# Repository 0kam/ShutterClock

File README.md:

<p align="center">
  <picture>
    <source media="(prefers-color-scheme: dark)" srcset="docs/assets/logo/logo_dark_800.png">
    
  </picture>
</p>

# ShutterClock

定点カメラ（タイムラプス・フェノロジー観測）用の低消費電力インターバルタイマです。
Nikon デジタル一眼レフをリモート端子から有線レリーズし、12 V ソーラー充電バッテリーからカメラへ給電することもできます。
時刻合わせ・撮影スケジュール設定・撮影ログ回収は、スマホ（Android Chrome）の Web Bluetooth ページで行います。
積雪深ロガー [SnowGauge](https://github.com/0kam/SnowGauge) の姉妹プロジェクトです。

*ShutterClock is a low-power BLE interval timer for fixed-point cameras: XIAO nRF52840 (Zephyr), wired Nikon remote release via optocouplers, optional camera power from a 12 V solar battery, Web Bluetooth field app. Documentation is in Japanese.*

## 状態（2026-10-11）

基板 v1.0 を JLCPCB に発注済み（5 枚、10 月中旬到着予定）、部品も発注済み。ファームウェア（`firmware/`、ビルド済み）とスマホアプリ（https://0kam.github.io/ShutterClock/app/ 、[デモ表示](https://0kam.github.io/ShutterClock/app/?demo=1)）の初版あり、実機検証はこれから。初期決定事項と未決事項を [設計仕様書 v0.17](ShutterClock_設計仕様書_v0.17.md) にまとめています。
対象機種は D7200・D7500（必須）と D7000・D7100・D800・D810（任意）。D7500 の消費電流は実測済み。次は部品・基板の到着後に実機でファームウェアを動かし、降圧モジュール・時計保持経路・撮影検出を確認します。

## 開発者向け

- 設計仕様書（要件・設計判断・未決事項・改版履歴）: [ShutterClock_設計仕様書_v0.17.md](ShutterClock_設計仕様書_v0.17.md)
- 部品購入リスト: [docs/01_parts.md](docs/01_parts.md)（[CSV](docs/01_parts.csv)、5 台分 [docs/01_order_5sets.csv](docs/01_order_5sets.csv)）
- 組み立てガイド（配置図・はんだ付け順・通電チェック）: [docs/02_assembly.md](docs/02_assembly.md)
- 基板: [pcb/README.md](pcb/README.md)（ピンマップの正）
- ファームウェア: [firmware/README.md](firmware/README.md)
- アプリ: [docs/app/README.md](docs/app/README.md)
- SnowGauge から流用したファイルの一覧: [PROVENANCE.md](PROVENANCE.md)
- 作業引き継ぎ（AI エージェント向け）: [CLAUDE.md](CLAUDE.md)

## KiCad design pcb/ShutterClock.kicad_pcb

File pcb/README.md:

# ShutterClock PCB

- **v1.2 (2026-10-21, not ordered)**: v1.1 + battery-backed RTC. Board grown to **100 x 100 mm**
  (mounting holes 93 x 93 mm); a 12 mm strip at the bottom carries **U5** Akizuki AE-RX8900
  (RX8900CE DTCXO RTC, I2C 0x32 on the XIAO D4 = SDA / D5 = SCL, VDD from 3V3_SYS, FOE tied to
  GND so FOUT stays off), **BT1** CH243-2032LF vertical CR2032 holder and **D7** 1N4148 in series
  with the cell (the RX8900 has an internal VDD -> VBAT charge path; a CR2032 must not be charged).
  SW1 and ZD1 moved 1-2 mm right to make room for the I2C / 3V3 tracks along the left edge.
  DRC 0 errors / 0 unconnected. `ShutterClock_v1.2_gerbers.zip`, `render_top.png`,
  `../docs/assembly/placement_top_v1.2.png`. **Open before ordering**: the holder's centre pin is
  assumed to be "+" (drawing CH243-0308 does not mark polarity) - check with a cell and a meter on
  the real part; if the outer pins are "+", swap BT1 pad nets in `generate_board.py`.
- **v1.1 (2026-10-21, not ordered)**: the three v1.0 errata fixed (C1 polarity nets, U2 hole
  pattern 40 x 17.5 mm, F1 clip pins along the fuse axis at 7.0 mm; ZD1 moved 3.5 mm down to make
  room). DRC 0 errors / 0 unconnected (40 silk warnings). Gerbers `ShutterClock_v1.1_gerbers.zip`,
  renders `render_top.png` / `render_bottom.png`, placement map `../docs/assembly/placement_top_v1.1.png`.
  Same outline, mounting holes and connector positions as v1.0, so the v1.0 bench results apply.
- **v1.0 (ordered 2026-10-08, JLCPCB W2026100808086019 / Y14-13437881A, 5 pcs; board #1 assembled
  and bench-tested 2026-10-20)**: `ShutterClock_v1.0_gerbers.zip`, `render_top_v1.0.png` /
  `render_bottom_v1.0.png`. Build the remaining v1.0 boards with the workarounds in
  `../docs/02_assembly.md`.

- Board: **100 x 88 mm**, 2-layer. Bottom layer is a GND pour; most signals on top,
  the VIN trunk and a few long signals on the bottom.
- Mounting: 4x M3 (3.2 mm) holes, centres 3.5 mm from each edge (93 x 81 mm spacing).
- Generated by [generate_board.py](generate_board.py) (+ [tracks.py](tracks.py)) →
  `ShutterClock.kicad_pcb` (KiCad 10). **Never hand-edit the .kicad_pcb.**
  Run: `/Applications/KiCad/KiCad.app/Contents/Frameworks/Python.framework/Versions/Current/bin/python3 generate_board.py`
  then `kicad-cli pcb drc --severity-error --severity-warning --format json --output drc.json ShutterClock.kicad_pcb`
  and `python3 drc_report.py`. Current state: **DRC 0 errors, 0 unconnected** (46 warnings: silkscreen overlaps, library-name notes).
- Gerbers for JLCPCB (2 layers, 1.6 mm, HASL, defaults): see the version list above. Export: `kicad-cli pcb export gerbers --layers F.Cu,B.Cu,F.Paste,B.Paste,F.Silkscreen,B.Silkscreen,F.Mask,B.Mask,Edge_Cuts --subtract-soldermask`, `kicad-cli pcb export drill --format excellon --excellon-units mm --generate-map --map-format gerberx2`, zip the folder. `kicad-cli` = `/Applications/KiCad/KiCad.app/Contents/MacOS/kicad-cli`.
- Circuit: spec v0.11 §6 (independent review applied). BOM: `../docs/01_parts.md`. Assembly guide: `../docs/02_assembly.md` (placement map generated by `../docs/assembly/draw_placement.py`).

## Errata v1.0 (fixed in v1.1)

1. **C1 silkscreen "+" is on the wrong pad.** `generate_board.py` assigns C1 pad 1 (the square
   pad, which the KiCad `CP_Radial` footprint marks "+") to GND and pad 2 to VIN. Electrically the
   board is fine; **mount C1 with its + lead in the right-hand (round) pad**. v1.1: swap the nets
   to `{"1": "VIN", "2": "GND"}` and re-route the two C1 tracks. C3 is correct (pad 1 = CAM_P).
2. **U2 (MBC2596-01) hole pattern is 40.0 x 17.5 mm** (measured on the real module 2026-10-19),
   not the 38 x 16 mm placeholder (±19.0 / ±8.0). v1.0 boards: the module is connected with bent
   tinned wire. v1.1: `fp_buck()` pads at ±20.0 / ±8.75 mm.
3. **F1 fuse clips (FUC-03A): the two pins of one clip lie ALONG the fuse axis**, not across it as
   in `fp_fuseclips()` (pairs 6.7 mm apart across the axis). v1.0 boards: cut one pin per clip and
   solder the other into one hole (keep the outer pin on one clip and the inner pin on the other
   so the clip spacing stays 18 mm), or put an inline fuse holder in the battery + lead and bridge
   the F1 holes. v1.1: rotate the footprint; pin pitch along the axis still to be measured.

## Open items (ordered before bench verification — check these when the boards arrive)

1. ~~U2 hole positions~~ → wrong, see Errata 2.
2. Bench-verify the circuit on the breadboard first (spec §6.5): LM2596 + 4700 µF with the
   D7500 (and D7200), keep-alive follower voltage, shot detection on A1.
3. Independent layout review (as for SnowGauge v1.2) — not done yet.
4. XIAO SMD-pad clearance to the KA_EN / CAM_EN tracks is at the 0.2 mm minimum; fine for
   JLCPCB but do not tighten.

## Firmware pin map (single source of truth for the board)

| XIAO pin | Net | Function |
|---|---|---|
| A0 (D0) | ADC_NODE | Battery voltage: VIN × 100k/(1M+100k) (ungated divider, 100 nF). Reading × 11 |
| A1 (D1) | A1_NODE | Camera current: 0.1 Ω low-side shunt in the camera return (CAM_N), 10 kΩ + 100 nF. 1 A = 0.1 V |
| D2 | AF_DRV | PC817 U4 (AF / half-press) via 1 kΩ. High = pressed |
| D7 | CAM_EN | Camera supply: Q3 → Q2 → MBC2596-01 (9.4 V) → 1N5822 → CAM_P. High = on |
| D8 | SHUT_DRV | PC817 U3 (SHUTTER / full-press) via 1 kΩ. High = pressed |
| D9 | BTN | Test-shot / BLE button SW1 to GND (enable the internal pull-up) |
| D10 | KA_EN | Keep-alive path: Q6 → Q5 → 10 Ω → Q7 follower (≈ 7.3–8.5 V) → CAM_P. High = on |
| 3V3 | 3V3_SYS | From U1 (NJW4181U3-33B) through JP1 |
| GND | GND | |
| D4 / D5 | SDA / SCL | v1.2: RX8900 RTC module U5 (i2c1). Unused on v1.0 / v1.1 |
| D3, D6, 5V | — | unused |

Rules: never drive CAM_EN and KA_EN so that the camera is released on the keep-alive
path; enter keep-alive only from CAM_EN = on; drop to CAM_EN = on if A1 shows > 50 mA
during keep-alive; low-battery cutoff 11.5 V.

## Connectors and jumpers

- J1 (5.08 mm screw terminal, bottom-left): battery + / − (12 V lead-acid / LiFePO4; fuse F1 5 A, Q1 reverse protection, 2x P4KE15A TVS)
- J2 (5.08 mm screw terminal, bottom-right): camera + / − → Nikon EP-5B cable. The − side is the sense shunt — keep it as the only camera ground.
- J3 (3.5 mm stereo jack, right edge): tip = SHUTTER, ring = AF, sleeve = common → off-the-shelf 3.5 mm → MC-DC2 / 10-pin release cables (verify the cable's pinout with a meter)
- JP1 (near the XIAO): shunt fitted normally; **remove before connecting USB** to the XIAO (same rule as SnowGauge)
- JP2 (below Q3): shunt fitted = camera supply always on (bypasses Q3)
- U2: 4-pin module socket positions; set the trimpot to **9.4 V** and remove the module's LED before fitting

## Silkscreen notes

"REMOVE JP1 BEFORE USB", "U2: SET 9.4V, REMOVE LED", "JP2=ALWAYS ON", battery and camera polarity, diode cathodes marked "K".

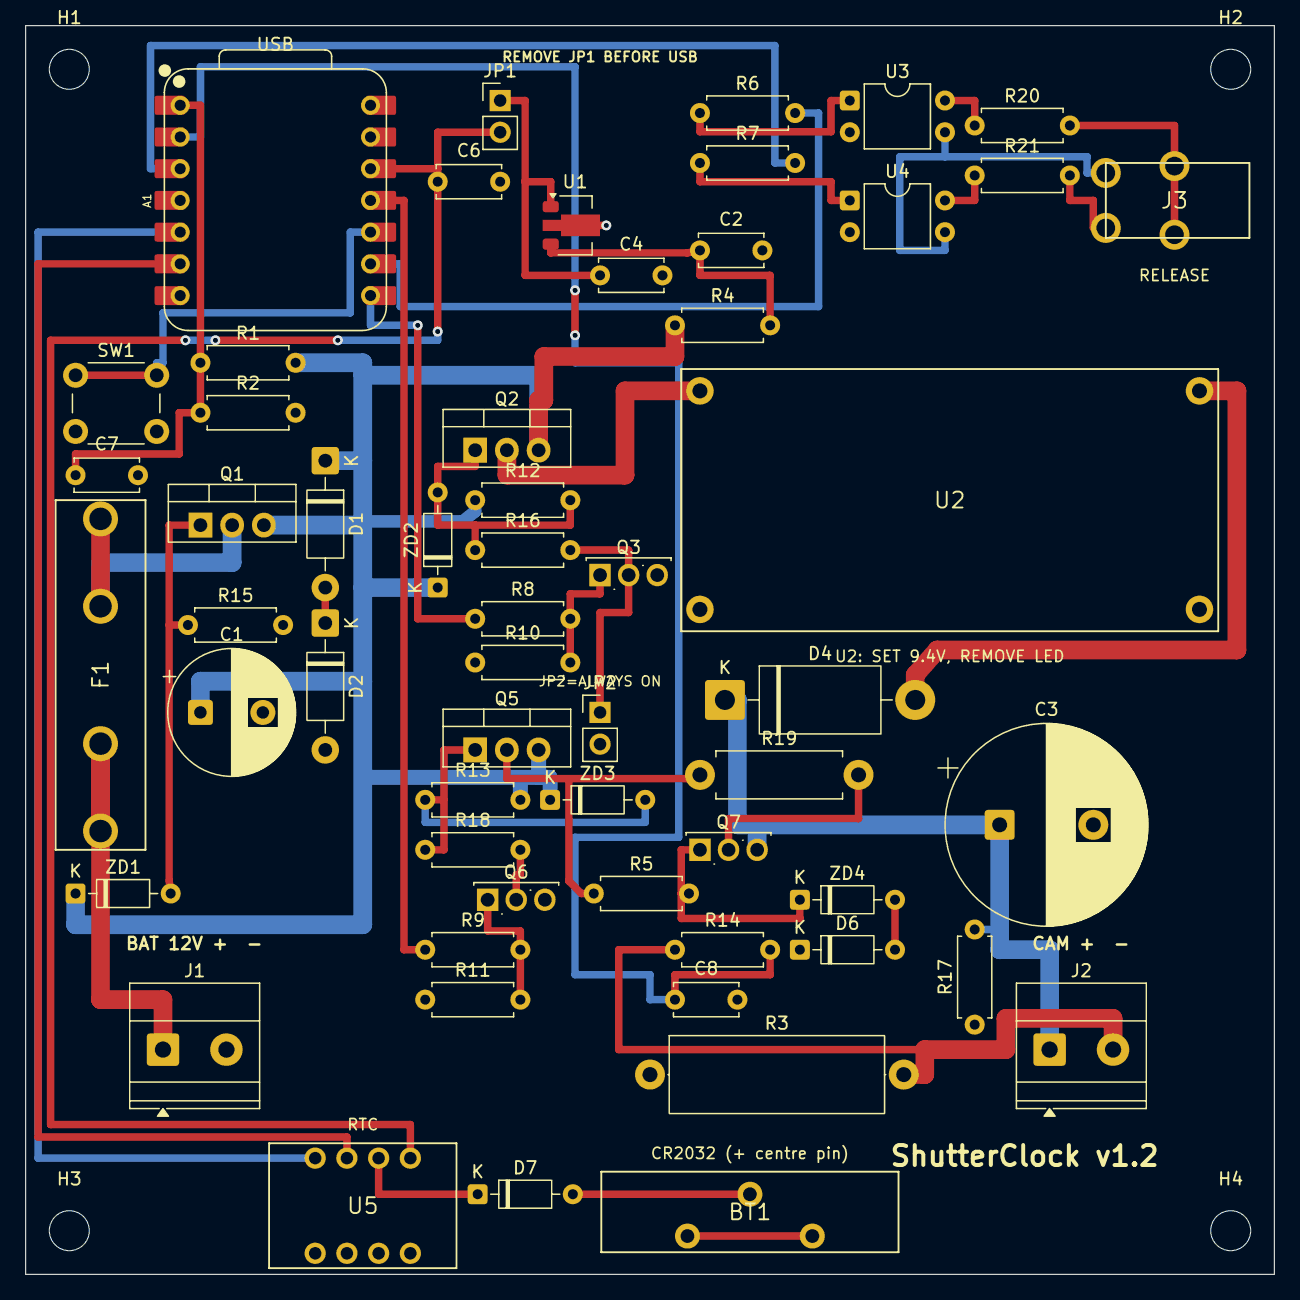
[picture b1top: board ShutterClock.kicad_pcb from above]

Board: 2 copper layers, 100.0 x 100.0 mm, 61 parts (0 on the bottom side), 41 nets.

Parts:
A1: XIAO nRF52840; XIAO-nRF52840-DIP
BT1: CR2032; CH243-2032LF
C1: 100u/50V; CP_Radial_D10.0mm_P5.00mm
C2: 10u; C_Disc_D5.0mm_W2.5mm_P5.00mm
C3: 4700u/16V; CP_Radial_D16.0mm_P7.50mm
C4: 2.2u; C_Disc_D5.0mm_W2.5mm_P5.00mm
C6, C7, C8: 0.1u; C_Disc_D5.0mm_W2.5mm_P5.00mm
D1, D2: P4KE15A; D_DO-41_SOD81_P10.16mm_Horizontal
D4: 1N5822; D_DO-201AD_P15.24mm_Horizontal
D6, D7: 1N4148; D_DO-35_SOD27_P7.62mm_Horizontal
F1: 5A; FUC-03A_x2_5x20
H1, H2, H3, H4: M3; MountingHole_3.2mm_M3
J1: BATTERY 12V; TerminalBlock_Phoenix_MKDS-1,5-2-5.08_1x02_P5.08mm_Horizont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
J2: CAMERA EP-5B; TerminalBlock_Phoenix_MKDS-1,5-2-5.08_1x02_P5.08mm_Horizont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
J3: 3.5mm RELEASE; MJ-8435
JP1: JP1 3V3; PinHeader_1x02_P2.54mm_Vertical
JP2: JP2 ALWAYS ON; PinHeader_1x02_P2.54mm_Vertical
Q1: 2SJ334 REV; TO-220-3_Vertical
Q2: 2SJ334 CAM; TO-220-3_Vertical
Q3, Q6: 2SK4017; TO-251-3_Vertical
Q5: 2SJ334 KA; TO-220-3_Vertical
Q7: 2SK4017 KA; TO-251-3_Vertical
R1, R15, R17: 1M; R_Axial_DIN0207_L6.3mm_D2.5mm_P7.62mm_Horizontal
R2, R10, R11, R12, R13: 100k; R_Axial_DIN0207_L6.3mm_D2.5mm_P7.62mm_Horizontal
R3: 0.1R 3W; R_Axial_DIN0617_L17.0mm_D6.0mm_P20.32mm_Horizontal
R4, R20, R21: 100; R_Axial_DIN0207_L6.3mm_D2.5mm_P7.62mm_Horizontal
R5: 47k; R_Axial_DIN0207_L6.3mm_D2.5mm_P7.62mm_Horizontal
R6, R7, R8, R9: 1k; R_Axial_DIN0207_L6.3mm_D2.5mm_P7.62mm_Horizontal
R14: 10k; R_Axial_DIN0207_L6.3mm_D2.5mm_P7.62mm_Horizontal
R16, R18: 33k; R_Axial_DIN0207_L6.3mm_D2.5mm_P7.62mm_Horizontal
R19: 10R 1W; R_Axial_DIN0411_L9.9mm_D3.6mm_P12.70mm_Horizontal
SW1: TEST; SW_PUSH_6mm
U1: NJW4181U3-33B; SOT-89-3
U2: MBC2596-01 9.4V; MBC2596-01
U3: PC817 SHUTTER; DIP-4_W7.62mm
U4: PC817 AF; DIP-4_W7.62mm
U5: AE-RX8900
ZD1, ZD2, ZD3: 15V; D_DO-35_SOD27_P7.62mm_Horizontal
ZD4: 9.1V; D_DO-35_SOD27_P7.62mm_Horizontal

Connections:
3V3_LDO: C4.1, JP1.1, U1.1
3V3_SYS: A1.12, C6.1, JP1.2, U5.8
A1_NODE: A1.2, C8.1, R14.2
ADC_NODE: A1.1, C7.1, R1.1, R2.1
AF_C: R21.1, U4.4
AF_DRV: A1.3, R7.2
AF_LED_A: R7.1, U4.1
BAT_RAW: F1.1, J1.1
BTN: A1.10, SW1.1
BT_P: BT1.1, D7.2
BUCK_IN: Q2.2, U2.INP
BUCK_OUT: D4.2, U2.OUTP
CAM_EN: A1.8, R8.1
CAM_N: J2.2, R3.2, R14.1
CAM_P: C3.1, D4.1, J2.1, Q7.3, R17.2
F_OUT: F1.2, Q1.2
GND: A1.13, BT1.2, C1.2, C2.2, C3.2, C4.2, C6.2, C7.2, C8.2, D2.2, D6.1, J1.2, JP2.2, Q3.3, Q6.3, R2.2, R3.1, R10.1, R11.1, R15.2, R17.1, SW1.2, U1.2, U2.INN, U2.OUTN, U3.2, U4.2, U5.1, U5.4
JACK_RING: J3.3, R21.2
JACK_SLEEVE: J3.1, U3.3, U4.3
JACK_TIP: J3.2, R20.2
KA_EN: A1.11, R9.1
KA_SW: Q5.2, R5.1, R19.1
LDO_IN: C2.1, R4.2, U1.3
Q1_G: Q1.1, R15.1, ZD1.2
Q2_DRV: JP2.1, Q3.2, R16.2
Q2_G: Q2.1, R12.2, R16.1, ZD2.2
Q3_G: Q3.1, R8.2, R10.2
Q5_DRV: Q6.2, R18.2
Q5_G: Q5.1, R13.1, R18.1, ZD3.2
Q6_G: Q6.1, R9.2, R11.2
Q7_D: Q7.2, R19.2
Q7_G: Q7.1, R5.2, ZD4.1
SCL: A1.6, U5.6
SDA: A1.5, U5.5
SHUT_C: R20.1, U3.4
SHUT_DRV: A1.9, R6.2
SHUT_LED_A: R6.1, U3.1
TVS_MID: D1.2, D2.1
VBAT_RTC: D7.1, U5.7
VIN: C1.1, D1.1, Q1.3, Q2.3, Q5.3, R1.2, R4.1, R12.1, R13.2, ZD1.1, ZD2.1, ZD3.1
ZD_MID: D6.2, ZD4.2

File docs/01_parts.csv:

区分,記号,部品,値/型番,数量,購入先リンク,備考
回路,A1,マイコン（BLE）,Seeed XIAO nRF52840（非Sense）,1,https://akizukidenshi.com/catalog/g/g117341/,¥1780。予備+1推奨
回路,U1,3.3V LDO（常時ON）,NJW4181U3-33B (SOT-89),1,https://akizukidenshi.com/catalog/g/g113996/,¥60。表面実装。ブレッドボードではAE-SOT89に載せる
回路,U2,カメラ用9V降圧,MBC2596-01 (LM2596-ADJ),2,https://akizukidenshi.com/catalog/g/g131750/,¥1900。1個予備。在庫僅少（10月中旬入荷）。9.4Vに調整・LED除去
回路,"Q1,Q2,Q5",P-ch MOSFET,2SJ334,3,https://akizukidenshi.com/catalog/g/g102846/,¥110。G-D-S
回路,"Q3,Q6,Q7",N-ch MOSFET,2SK4017(Q),3,https://akizukidenshi.com/catalog/g/g107597/,¥30。G-D-S
回路,"ZD1,ZD2,ZD3",15Vツェナー,GDZJ15C 500mW,3,https://akizukidenshi.com/catalog/g/g115169/,10本¥90
回路,ZD4,9.1Vツェナー（時計保持フォロワ基準）,BZX55C9V1 500mW,1,https://akizukidenshi.com/catalog/g/g115721/,20本¥100。1N4148と直列
回路,D6,ZD4と直列,1N4148,1,https://akizukidenshi.com/catalog/g/g100941/,50本¥200
回路,"D1,D2",TVS（2本直列）,P4KE15A,2,https://akizukidenshi.com/catalog/g/g129633/,10本¥150
回路,D4,ショットキー（U2出力逆流防止）,1N5822 40V3A,1,https://akizukidenshi.com/catalog/g/g102229/,10本¥350
回路,F1,ヒューズ,MF51NR 250V5A 5.2x20mm,1,https://akizukidenshi.com/catalog/g/g107131/,¥40
回路,F1ホルダ,ヒューズクリップ,FUC-03A,2,https://akizukidenshi.com/catalog/g/g110521/,¥20。2個で1本分
回路,R3,電流検出抵抗,0.1Ω 3W ±1% RSMF3BR100F,1,https://akizukidenshi.com/catalog/g/g111011/,¥20
回路,"U3,U4",フォトカプラ,PC817 (PC817X3NSZ1B),2,https://akizukidenshi.com/catalog/g/g113765/,¥30。在庫僅少。代替UPC817CG 116090
回路,J3,3.5mmステレオジャック,MJ-8435,1,https://akizukidenshi.com/catalog/g/g109060/,¥90
回路,"JP1,JP2",ジャンパ（USB時外す/常時ON）,ピンヘッダ1x2+ジャンパピン,2,https://akizukidenshi.com/catalog/g/g103691/,ジャンパピンのコード要確認
回路,SW1,タクトスイッチ,6mm DTS-63-N-V-BLK,1,https://akizukidenshi.com/catalog/g/g103647/,¥15
回路,C1,入力バルク,100μF/50V ハイブリッド Rubycon PZF,1,https://akizukidenshi.com/catalog/g/g116871/,¥80
回路,C2,U1入力RC,10μF/50V 積セラ 5mm,1,https://akizukidenshi.com/catalog/g/g108155/,¥60
回路,C3,カメラ9V側バルク,4700μF/16V Rubycon ZLH,1,https://akizukidenshi.com/catalog/g/g114096/,¥100
回路,C4,U1出力,2.2μF/50V 積セラ 5mm,1,https://akizukidenshi.com/catalog/g/g108152/,¥30
回路,C6-C8,パスコン・ADCフィルタ,0.1μF/50V 積セラ,3,https://akizukidenshi.com/catalog/g/g113582/,10個¥100
回路,R4,U1入力RC,100Ω 1/4W,1,https://akizukidenshi.com/catalog/g/g125101/,100本¥200
回路,"R20,R21",J3チップ/リング直列,100Ω 1/4W,2,https://akizukidenshi.com/catalog/g/g125101/,R4と同じ袋
回路,"R6-R9",フォトカプラLED直列/ゲート直列,1kΩ 1/4W,4,https://akizukidenshi.com/catalog/g/g125102/,100本¥100
回路,"R10-R13,R2",プルダウン/プルアップ/分圧下,100kΩ 1/4W,5,https://akizukidenshi.com/catalog/g/g125104/,100本¥200
回路,R5,ZD4バイアス（KA_SWから）,47kΩ 1/4W,1,https://akizukidenshi.com/catalog/g/g125473/,100本¥200。コード要確認
回路,"R16,R18",Q2/Q5ゲート直列,33kΩ 1/4W,2,https://akizukidenshi.com/catalog/g/g125333/,100本¥200
回路,R19,Q7ドレイン突入制限,10Ω 1W カーボン,1,https://akizukidenshi.com/catalog/g/g107956/,100本¥350
回路,"R1,R15,R17",分圧上/Q1ゲート/C3ブリーダ,1MΩ 1/4W,3,https://akizukidenshi.com/catalog/g/g125105/,100本¥200
回路,R14,A1フィルタ,10kΩ 1/4W,1,https://akizukidenshi.com/catalog/g/g125103/,100本¥100
ブレッドボード,-,ブレッドボード830穴,EIC-102BJ,1,https://akizukidenshi.com/catalog/g/g100285/,¥1980
ブレッドボード,-,ジャンパワイヤ,60本以上セット,1,https://akizukidenshi.com/catalog/g/g130088/,¥300
ブレッドボード,-,SOT-89変換基板,AE-SOT89,1,https://akizukidenshi.com/catalog/g/g110835/,10枚¥70
ブレッドボード,-,ピンヘッダ1x40,PH-1x40SG,1,https://akizukidenshi.com/catalog/g/g100167/,¥35
カメラ側,-,ダミーバッテリー,Nikon EP-5B,1,https://www.amazon.co.jp/dp/B0042VJSN8,¥2318
カメラ側,-,レリーズケーブル（D7000-D7500）,3.5mm → MC-DC2型（3.5mm-N3）,1,https://www.amazon.co.jp/dp/B0C9YLTTSX,¥926
カメラ側,-,レリーズケーブル（D800/D810 任意）,2.5mm → 10ピン,1,https://www.amazon.co.jp/dp/B0D49L1SL3,¥1701
カメラ側,-,変換アダプタ（D800/D810 任意）,2.5mmメス → 3.5mmオス,1,https://www.amazon.co.jp/dp/B00KXMH1UW,¥580
PCB,"J1,J2",ネジ端子2P 5.08mm,TB111-2,2,https://akizukidenshi.com/catalog/g/g102333/,¥40
PCB,A1ソケット,ピンソケット1x7,FH-1x7SG/RH,2,https://akizukidenshi.com/catalog/g/g104285/,¥20
PCB,U2ソケット,ピンソケット1x4,FH-1x4SG/RH,1,https://akizukidenshi.com/catalog/g/g110099/,¥20
PCB,-,OS-CON 470μF/16V（任意）,16SEPC470M,1,https://akizukidenshi.com/catalog/g/g108292/,¥80

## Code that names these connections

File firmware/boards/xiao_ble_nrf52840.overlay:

/*
 * ShutterClock board overlay for Seeed XIAO nRF52840 (non-Sense) on PCB v1.0.
 * Pin map source of truth: pcb/README.md
 *
 *   A0  (P0.02) ADC_NODE   VIN x 100k/(1M+100k), ungated, 100 nF
 *   A1  (P0.03) A1_NODE    camera return current: 0.1 ohm shunt, 10k + 100 nF
 *   D2  (P0.28) AF_DRV     PC817 U4 -> jack ring (half press)
 *   D7  (P1.12) CAM_EN     Q3 -> Q2 -> buck module (camera 9 V)
 *   D8  (P1.13) SHUT_DRV   PC817 U3 -> jack tip (full press)
 *   D9  (P1.14) BTN        test-shot button to GND
 *   D10 (P1.15) KA_EN      Q6 -> Q5 -> keep-alive follower
 */

#include <zephyr/dt-bindings/adc/adc.h>
#include <zephyr/dt-bindings/i2c/i2c.h>
#include <zephyr/dt-bindings/adc/nrf-adc.h>

/*
 * The board DTS enables uart0 (D6/D7), spi2 (D8/D9/D10) and i2c1 (D4/D5).
 * Their pinctrl would claim CAM_EN, SHUTTER, BTN and KA_EN, so the GPIO
 * outputs never reach the pins (found on the first board, 2026-10-20).
 */
&uart0 {
	status = "disabled";
};

&spi2 {
	status = "disabled";
};

/* PCB v1.2: RX8900 RTC module on D4 (SDA) / D5 (SCL). Probed at boot; absent on v1.0/v1.1. */
&i2c1 {
	status = "okay";
	clock-frequency = <I2C_BITRATE_STANDARD>;
	rx8900: rx8900@32 {
		compatible = "epson,rx8900";
		reg = <0x32>;
		status = "okay";
	};
};

/ {
	zephyr,user {
		cam-en-gpios = <&xiao_d 7 GPIO_ACTIVE_HIGH>;
		ka-en-gpios = <&xiao_d 10 GPIO_ACTIVE_HIGH>;
		af-gpios = <&xiao_d 2 GPIO_ACTIVE_HIGH>;
		shutter-gpios = <&xiao_d 8 GPIO_ACTIVE_HIGH>;
		button-gpios = <&xiao_d 9 (GPIO_ACTIVE_LOW | GPIO_PULL_UP)>;
		io-channels = <&adc 0>, <&adc 1>;
	};
};

&adc {
	status = "okay";
	#address-cells = <1>;
	#size-cells = <0>;

	/* Battery divider: node = VIN / 11, 2.7 V at 30 V. FS 0.6 V x 6 = 3.6 V. */
	channel@0 {
		reg = <0>;
		zephyr,gain = "ADC_GAIN_1_6";
		zephyr,reference = "ADC_REF_INTERNAL";
		zephyr,acquisition-time = <ADC_ACQ_TIME(ADC_ACQ_TIME_MICROSECONDS, 40)>;
		zephyr,input-positive = <NRF_SAADC_AIN0>;
		zephyr,resolution = <12>;
		zephyr,oversampling = <4>;
	};

	/* Camera current: 0.1 ohm shunt, FS 0.6 V = 6 A, 1.46 mA/LSB at 12 bit. */
	channel@1 {
		reg = <1>;
		zephyr,gain = "ADC_GAIN_1";
		zephyr,reference = "ADC_REF_INTERNAL";
		zephyr,acquisition-time = <ADC_ACQ_TIME(ADC_ACQ_TIME_MICROSECONDS, 10)>;
		zephyr,input-positive = <NRF_SAADC_AIN1>;
		zephyr,resolution = <12>;
		zephyr,oversampling = <2>;
	};
};

/* nRF52 die temperature (record field temp_dc). */
&temp {
	status = "okay";
};

/*
 * Record storage: QSPI (2 MB P25Q16H), one LittleFS partition over the whole
 * chip; runtime PM keeps the chip in deep power-down between accesses.
 */
&p25q16h {
	zephyr,pm-device-runtime-auto;

	partitions {
		compatible = "fixed-partitions";
		#address-cells = <1>;
		#size-cells = <1>;

		lfs1_part: partition@0 {
			label = "lfs";
			reg = <0x00000000 0x00200000>;
		};
	};
};

/ {
	fstab {
		compatible = "zephyr,fstab";

		lfs1: lfs1 {
			compatible = "zephyr,fstab,littlefs";
			mount-point = "/lfs1";
			partition = <&lfs1_part>;
			read-size = <16>;
			prog-size = <16>;
			cache-size = <64>;
			lookahead-size = <32>;
			block-cycles = <512>;
		};
	};

	/* Emulated calendar clock behind the `rtc` alias (timekeeping.c, mcumgr datetime). */
	rtc_emul: rtc-emul {
		compatible = "zephyr,rtc-emul";
		status = "okay";
	};

	aliases {
		rtc = &rtc_emul;
		extrtc = &rx8900;
	};
};

/*
 * Internal flash (1 MB), same layout as SnowGauge:
 *   0x00000  156 kB  Adafruit bootloader + SoftDevice area (untouched)
 *   0x27000  480 kB  Application (this image)
 *   0x9F000  308 kB  mirror_partition (raw append-only records)
 *   0xEC000   32 kB  storage_partition (settings)
 *   0xF4000   48 kB  bootloader UF2 area (untouched)
 */
&code_partition {
	reg = <0x00027000 0x00078000>;
};

&flash0 {
	partitions {
		mirror_partition: partition@9f000 {
			label = "mirror";
			reg = <0x0009f000 0x0004d000>;
		};
	};
};
